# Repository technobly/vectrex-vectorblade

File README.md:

Vectrex Vectorblade PCB by Brett Walach
===

[Malban's Vectorblade PCB design](http://vide.malban.de/vectorblade/building-vectorblade/vectorblade-build-the-hardware), optimized with single gate SMT IC's (AND & NOT), 8 color RGB LED, and some gorgeous artwork applied.  Looks great in black soldermask with ENIG (gold flash) finish!

Yes these fit in [Sean Kelly reproduction cartridge shells](http://www.vectrexmulti.com/order2.html#!/Vectrex-Empty-Cartridge-Shells/c/38886086/offset=0&sort=normal) perfectly!

BOM and Parts ordering
===

All the parts are described in [Bill of Materials](bom/)

You can use this Digi-Key shared cart to order the parts!
[Vectrex Vectorblade](https://www.digikey.com/short/90np89zn)

Ordering PCB's
===

OSHPark is a good place to order with purple or the new "after dark" theme color scheme.  You can upload the KiCad `vextrex-vectorblade.kicad_pcb` there directly.  I would download this entire Github repo ZIP file first though instead of just trying to save the PCB file from your browser.

Another way to order PCB's is by using the included [gerbers](gerbers/vectrex-vectorblade-v1.0.zip) and uploading those with all of the necessary specs to companies like [PCBWay](https://www.pcbway.com) or [JLCPCB](https://jlcpcb.com)

Don't forget to make your board finish at least ENIG (gold flash) with a 45 degree chamfered edge.

LICENSE
===

CERN OHL v2.0 Permissive - essentially do whatever you want, but if you make a ton of money off of this... [buy me a coffee please!](https://buymeacoffee.com/walach)  Full [LICENSE here](LICENSE)

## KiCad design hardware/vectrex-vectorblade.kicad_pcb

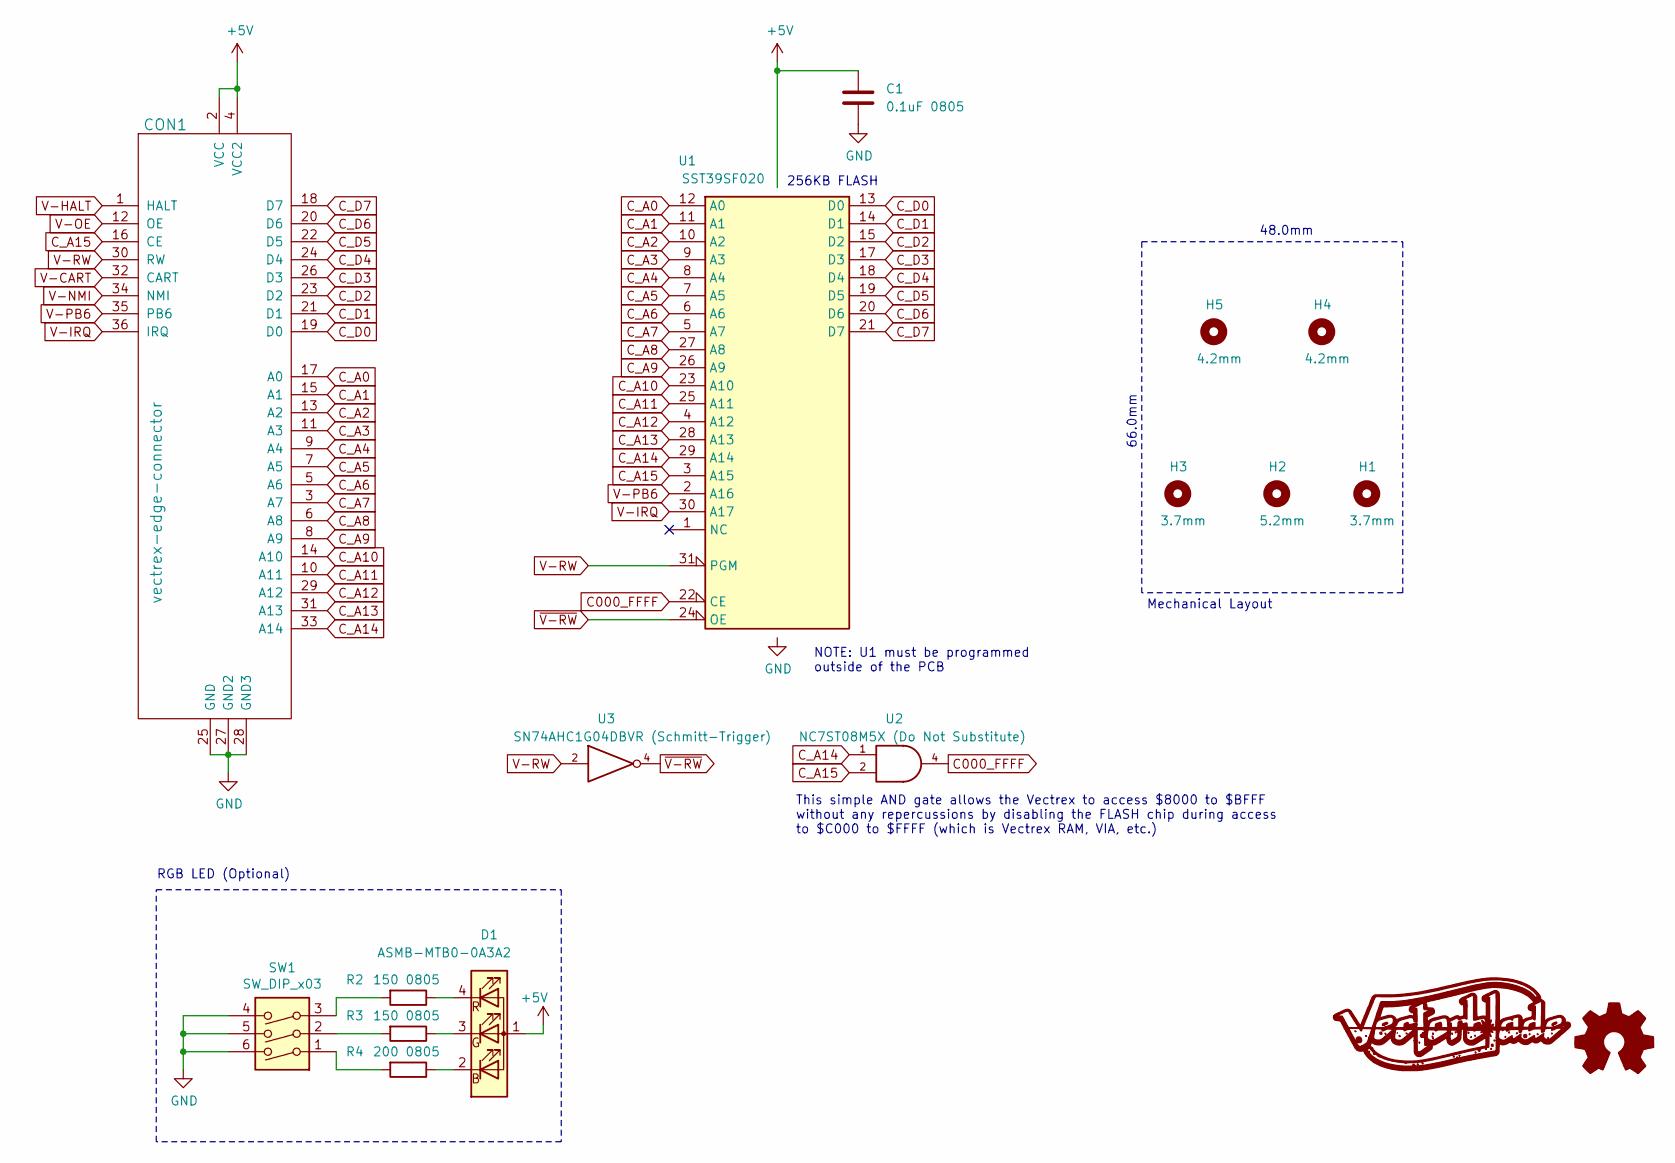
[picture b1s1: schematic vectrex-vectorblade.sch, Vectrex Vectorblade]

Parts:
C1: 0.1uF 0805; C_0805_2012Metric_Pad1.15x1.40mm_HandSolder
CON1: vectrex-edge-connector; vectrex-edge-connector-thinner-no-soldermask
D1: ASMB-MTB0-0A3A2; LED_Avago_PLCC4_3.2x2.8mm_CW
H1, H3: 3.7mm; Mounting_Hole_D3.7mm
H2: 5.2mm; Mounting_Hole_D5.2mm
H4, H5: 4.2mm; Mounting_Hole_D4.2mm
R2, R3: 150 0805; R_0805_2012Metric_Pad1.15x1.40mm_HandSolder
R4: 200 0805; R_0805_2012Metric_Pad1.15x1.40mm_HandSolder
SW1: SW_DIP_x03; SW_DIP_SPSTx03_Slide_6.7x9.18mm_W8.61mm_P2.54mm_LowProfile
U1: SST39SF020; DIP-32_W15.24mm_Socket
U2: NC7ST08M5X (Do Not Substitute); SOT-23-5_HandSoldering
U3: SN74AHC1G04DBVR (Schmitt-Trigger); SOT-23-5_HandSoldering

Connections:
+5V: C1.1, CON1.2 (VCC), CON1.4 (VCC2), D1.1 (A), U1.32 (VCC), U2.5 (VCC), U3.5 (VCC)
C000_FFFF: U1.22 (CE), U2.4
C_A0: CON1.17 (A0), U1.12 (A0)
C_A1: CON1.15 (A1), U1.11 (A1)
C_A2: CON1.13 (A2), U1.10 (A2)
C_A3: CON1.11 (A3), U1.9 (A3)
C_A4: CON1.9 (A4), U1.8 (A4)
C_A5: CON1.7 (A5), U1.7 (A5)
C_A6: CON1.5 (A6), U1.6 (A6)
C_A7: CON1.3 (A7), U1.5 (A7)
C_A8: CON1.6 (A8), U1.27 (A8)
C_A9: CON1.8 (A9), U1.26 (A9)
C_A10: CON1.14 (A10), U1.23 (A10)
C_A11: CON1.10 (A11), U1.25 (A11)
C_A12: CON1.29 (A12), U1.4 (A12)
C_A13: CON1.31 (A13), U1.28 (A13)
C_A14: CON1.33 (A14), U1.29 (A14), U2.1
C_A15: CON1.16 (CE), U1.3 (A15), U2.2
C_D0: CON1.19 (D0), U1.13 (D0)
C_D1: CON1.21 (D1), U1.14 (D1)
C_D2: CON1.23 (D2), U1.15 (D2)
C_D3: CON1.26 (D3), U1.17 (D3)
C_D4: CON1.24 (D4), U1.18 (D4)
C_D5: CON1.22 (D5), U1.19 (D5)
C_D6: CON1.20 (D6), U1.20 (D6)
C_D7: CON1.18 (D7), U1.21 (D7)
GND: C1.2, CON1.25 (GND), CON1.27 (GND2), CON1.28 (GND3), SW1.4, SW1.5, SW1.6, U1.16 (GND), U2.3 (GND), U3.3 (GND)
unnamed: D1.2 (BK), R4.1
unnamed: D1.3 (GK), R3.1
unnamed: D1.4 (RK), R2.1
unnamed: R2.2, SW1.3
unnamed: R3.2, SW1.2
unnamed: R4.2, SW1.1
V-CART: CON1.32 (CART)
V-HALT: CON1.1 (HALT)
V-IRQ: CON1.36 (IRQ), U1.30 (A17)
V-NMI: CON1.34 (NMI)
V-OE: CON1.12 (OE)
V-PB6: CON1.35 (PB6), U1.2 (A16)
V-RW: CON1.30 (RW), U1.31 (PGM), U3.2
~V-RW: U1.24 (OE), U3.4

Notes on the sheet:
256KB FLASH
NOTE: U1 must be programmed outside of the PCB
RGB LED (Optional)
48.0mm
66.0mm
This simple AND gate allows the Vectrex to access $8000 to $BFFF without any repercussions by disabling the FLASH chip during access to $C000 to $FFFF (which is Vectrex RAM, VIA, etc.)
Mechanical Layout

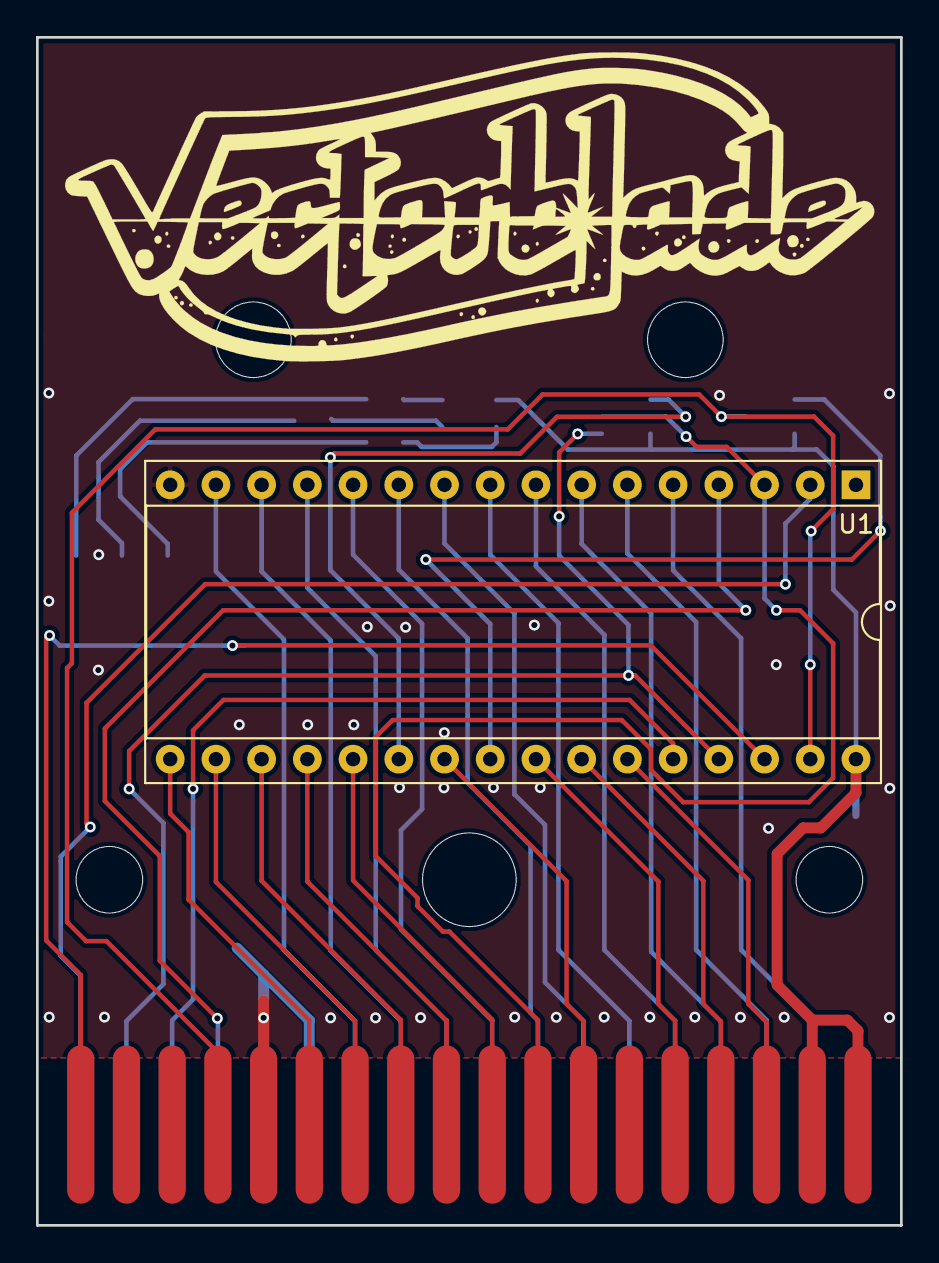
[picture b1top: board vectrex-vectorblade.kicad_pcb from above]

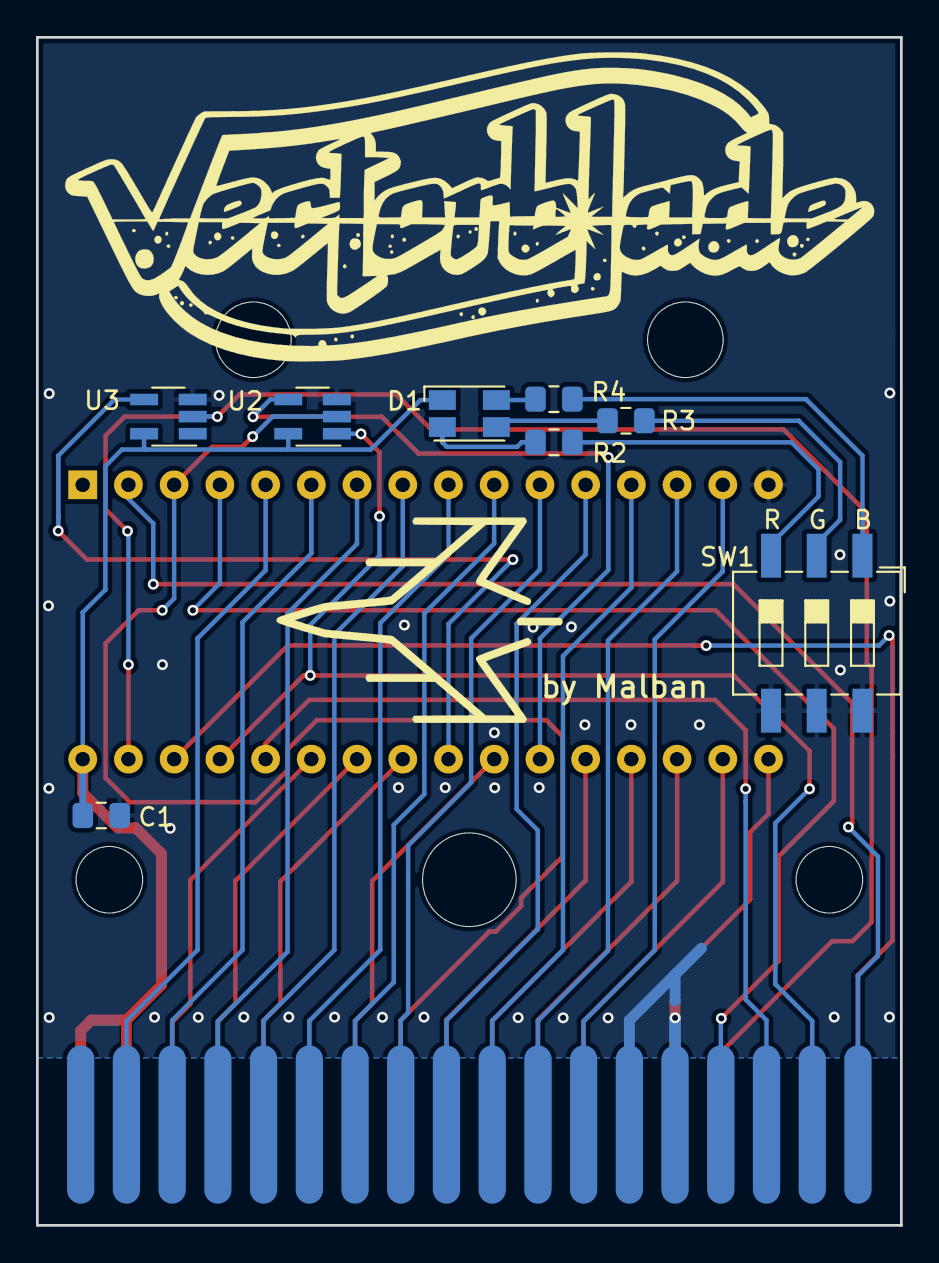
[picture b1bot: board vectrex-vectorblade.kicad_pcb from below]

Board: 2 copper layers, 48.0 x 66.0 mm, 15 parts (8 on the bottom side), 37 nets.

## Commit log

2022-02-20 initial commit v1.0
